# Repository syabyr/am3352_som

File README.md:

# am3352_som

#### 管脚定义

|管脚|定义|定义|管脚|
|----|---|----|---|
|1|GND|GND|2|
|3|LCD_DATA4|LCD_DATA8|4|
|5|GND|LCD_DATA5|6|
|7|LCD_DATA0|GND|8|
|9|LCD_DATA1|LCD_DATA2|10|
|11|GND|LCD_DATA6|12|
|13|LCD_PCLK|GND|14|
|15|LCD_VSYNC|LCD_DATA3|16|
|17|GND|LCD_DATA7|18|
|19|LCD_DATA14|GND|20|
|21|LCD_DATA11|LCD_HSYNC|22|
|23|GND|LCD_DATA15|24|
|25|LCD_DATA13|GND|26|
|27|LCD_DATA10|LCD_AC_BIAS_EN|28|
|29|GND|GPMC_AD8|30|
|31|LCD_DATA12|GND|32|
|33|LCD_DATA9|GPMC_AD9|34|
|35|GND|GPMC_AD10|36|
|37|GPMC_CLK|GND|38|
|39|GPMC_AD11|GPMC_13|40|
|41|GND|GPMC_12|42|
|43|GPMC_AD14|GND|44|
|45|GPMC_AD15|GPMC_A0|46|
|47|GND|GPMC_A4|48|
|49|GPMC_A2|GND|50|
|51|GPMC_A5|GPMC_A3|52|
|53|GND|GPMC_A1|54|
|55|GPMC_A6|GND|56|
|57|GPMC_A8|GPMC_A7|58|
|59|GND|GPMC_A10|60|
|61|GPMC_A9|GND|62|
|63|GPMC_A11|GPMC_BEn1|64|
|65|GND|USB1_VBUS|66|
|67|USB1_DP|GND|68|
|69|USB1_DM|USB0_VBUS|70|
|71|GND|USB0_ID|72|
||||
|73|USB1_ID|GND|74|
|75|USB1_CE|USB0_CE|76|
|77|GND|MDIO|78|
|79|USB0_DP|GND|80|
|81|USB0_DM|MDC|82|
|83|GND|MII1_RXD0|84|
|85|MII1_RXD3|GND|86|
|87|MII1_RX_CLK|MII1_RXD2|88|
|89|GND|MII1_RXD1|90|
|91|MII1_RX_DV|GND|92|
|93|MII1_TX_CLK|MII1_TXD2|94|
|95|GND|MII1_TXD0|96|
|97|MII1_TXD3|GND|98|
|99|MII1_TX_EN|MII1_TXD1|100|
|101|GND|MII1_RX_ER|102|
|103|RMII1_REF_CLK|GND|104|
|105|MMC0_CMD|MII1_COL|106|
|107|GND|MII1_CRS|108|
|109|MMC0_DAT2|GND|110|
|111|MMC0_DAT3|MMC0_DAT0|112|
|113|GND|MMC0_CLK|114|
|115|UART0_RTSn|GND|116|
|117|UART1_CSTn|MMC0_DAT1|118|
|119|GND|USB0_DRVVBUS|120|
|121|UART1_RTSn|GND|122|
|123|ECAP0_IN_PWM0_OUT|USB1_DRVVBUS|124|
|125|GND|UART0_TXD|126|
|127|I2C0_SDA|GND|128|
|129|EXTINTn|UART0_RXD|130|
|131|GND|UART1_RXD|132|
|133|SPI0_D0|GND|134|
|135|SPI0_SCLK|UART1_TXD|136|
|137|GND|I2C0_SCL|138|
|139|SPI0_D0|GND|140|
|141|SPI0_CS0|SPI0_CS1|142|
|143|GND|XDMA_EVENT_INTR1|144|
|145|EMU1|GND|146|
|147|MCASP0_AHCLKX|EMU0|148|
|149|GND|MCASP0_AXR1|150|
|151|MCASP0_FSX|GND|152|
|153|MCASP0_ACLKX|MCASP0_FSR|154|
|155|GND|MCASP0_AXR0|156|
|157|MCASP0_ACLKR|GND|158|
|159|TCK|MCASP0_AHCLKR|160|
|161|GND|TMS|162|
|163|TDI|GND|164|
|165|TDO|AIN7|166|
|167|GND|AIN4|168|
|169|TRSTn|GND|170|
|171|WARMRSTn|AIN5|172|
|173|GND|AIN6|174|
|175|PMIC_POWER_EN|GND|176|
|177|RTC_PWRONRSTn|AIN1|178|
|179|GND|AIN3|180|
|181|EXT_WAKEUP|GND|182|
|183|VDDS_RTC|AIN2|184|
|185|GND|AIN0|186|
|187||GND|188|
|189|VREFP|VCC|190|
|191|VCC|VCC|192|
|193|VCC|VCC|194|
|195|VCC|VCC|196|
|197|VCC|VCC|198|
|199|VCC|VCC|200|
|201|VCC|VCC|202|
|203|VCC|VCC|204|

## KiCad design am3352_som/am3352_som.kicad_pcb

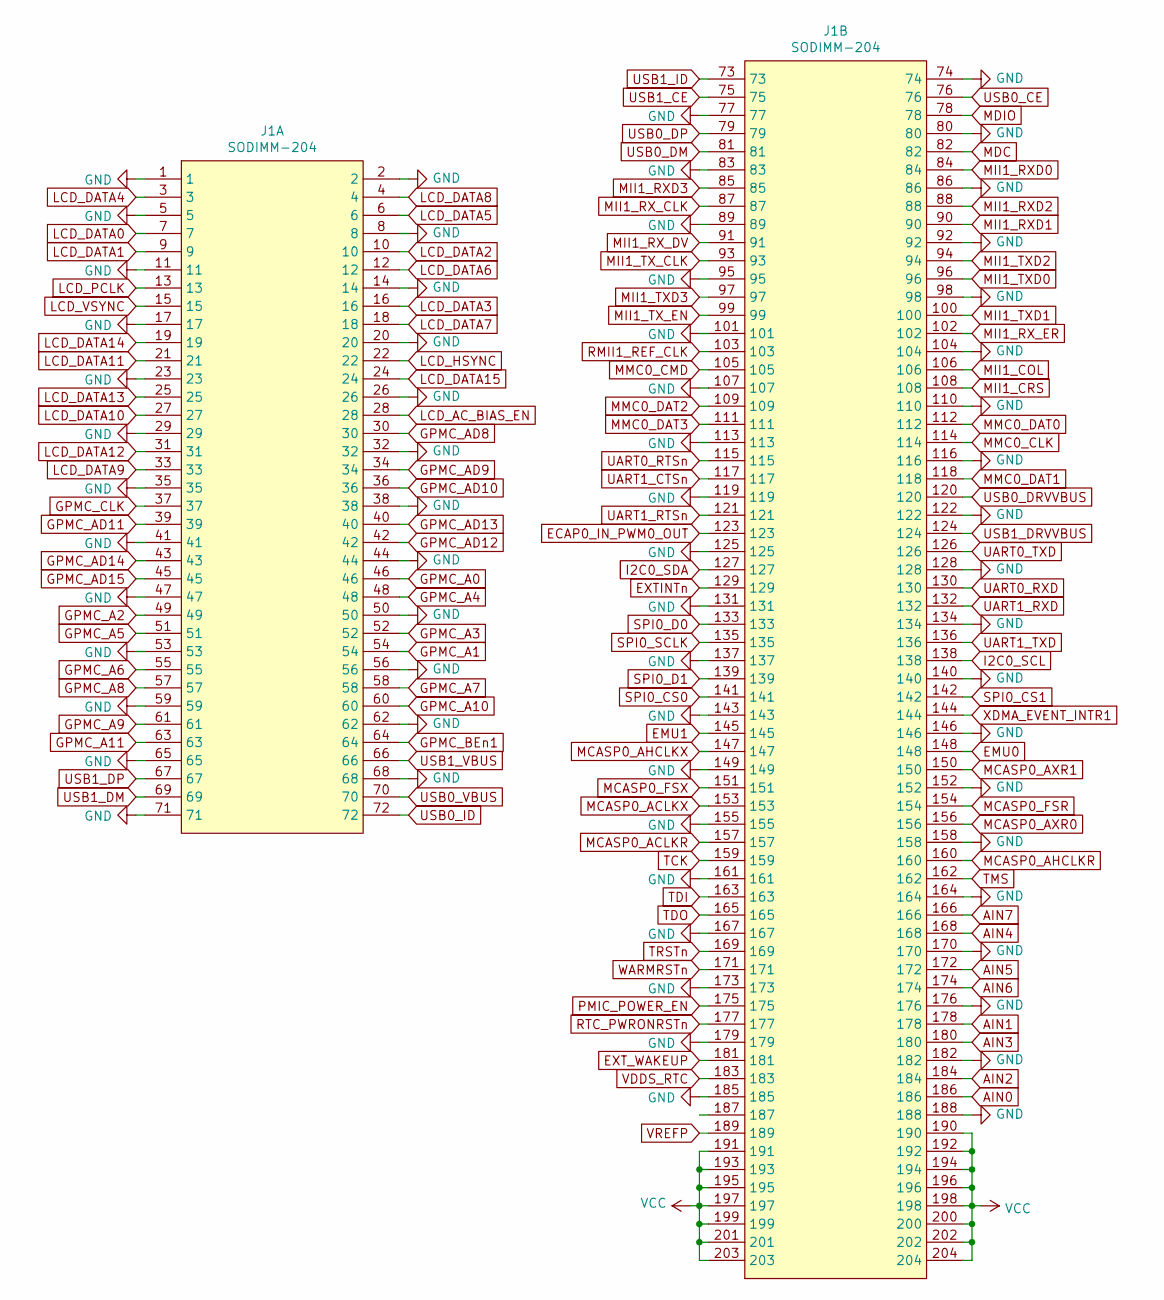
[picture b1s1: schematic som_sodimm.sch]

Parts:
J1: SODIMM-204; Socket_SODIMM_DDR3_TE_2013289_Debug

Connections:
AIN0: J1.186
AIN1: J1.178
AIN2: J1.184
AIN3: J1.180
AIN4: J1.168
AIN5: J1.172
AIN6: J1.174
AIN7: J1.166
ECAP0_IN_PWM0_OUT: J1.123
EMU0: J1.148
EMU1: J1.145
EXTINTn: J1.129
EXT_WAKEUP: J1.181
GND: J1.1, J1.2, J1.5, J1.8, J1.11, J1.14, J1.17, J1.20, J1.23, J1.26, J1.29, J1.32, J1.35, J1.38, J1.41, J1.44, J1.47, J1.50, J1.53, J1.56, J1.59, J1.62, J1.65, J1.68, J1.71, J1.74, J1.77, J1.80, J1.83, J1.86, J1.89, J1.92, J1.95, J1.98, J1.101, J1.104, J1.107, J1.110, J1.113, J1.116, J1.119, J1.122, J1.125, J1.128, J1.131, J1.134, J1.137, J1.140, J1.143, J1.146, J1.149, J1.152, J1.155, J1.158, J1.161, J1.164, J1.167, J1.170, J1.173, J1.176, J1.179, J1.182, J1.185, J1.188; also elsewhere on the board
GPMC_A0: J1.46
GPMC_A1: J1.54
GPMC_A2: J1.49
GPMC_A3: J1.52
GPMC_A4: J1.48
GPMC_A5: J1.51
GPMC_A6: J1.55
GPMC_A7: J1.58
GPMC_A8: J1.57
GPMC_A9: J1.61
GPMC_A10: J1.60
GPMC_A11: J1.63
GPMC_AD8: J1.30
GPMC_AD9: J1.34
GPMC_AD10: J1.36
GPMC_AD11: J1.39
GPMC_AD12: J1.42
GPMC_AD13: J1.40
GPMC_AD14: J1.43
GPMC_AD15: J1.45
GPMC_BEn1: J1.64
GPMC_CLK: J1.37
I2C0_SCL: J1.138
I2C0_SDA: J1.127
LCD_AC_BIAS_EN: J1.28
LCD_DATA0: J1.7
LCD_DATA1: J1.9
LCD_DATA2: J1.10
LCD_DATA3: J1.16
LCD_DATA4: J1.3
LCD_DATA5: J1.6
LCD_DATA6: J1.12
LCD_DATA7: J1.18
LCD_DATA8: J1.4
LCD_DATA9: J1.33
LCD_DATA10: J1.27
LCD_DATA11: J1.21
LCD_DATA12: J1.31
LCD_DATA13: J1.25
LCD_DATA14: J1.19
LCD_DATA15: J1.24
LCD_HSYNC: J1.22
LCD_PCLK: J1.13
LCD_VSYNC: J1.15
MCASP0_ACLKR: J1.157
MCASP0_ACLKX: J1.153
MCASP0_AHCLKR: J1.160
MCASP0_AHCLKX: J1.147
MCASP0_AXR0: J1.156
MCASP0_AXR1: J1.150
MCASP0_FSR: J1.154
MCASP0_FSX: J1.151
MDC: J1.82
MDIO: J1.78
MII1_COL: J1.106
MII1_CRS: J1.108
MII1_RXD0: J1.84; also elsewhere on the board
MII1_RXD1: J1.90; also elsewhere on the board
MII1_RXD2: J1.88; also elsewhere on the board
MII1_RXD3: J1.85; also elsewhere on the board
MII1_RX_CLK: J1.87
MII1_RX_DV: J1.91; also elsewhere on the board
MII1_RX_ER: J1.102
MII1_TXD0: J1.96; also elsewhere on the board
MII1_TXD1: J1.100; also elsewhere on the board
MII1_TXD2: J1.94; also elsewhere on the board
MII1_TXD3: J1.97; also elsewhere on the board
MII1_TX_CLK: J1.93; also elsewhere on the board
MII1_TX_EN: J1.99; also elsewhere on the board
MMC0_CLK: J1.114; also elsewhere on the board
MMC0_CMD: J1.105; also elsewhere on the board
MMC0_DAT0: J1.112; also elsewhere on the board
MMC0_DAT1: J1.118; also elsewhere on the board
MMC0_DAT2: J1.109; also elsewhere on the board
MMC0_DAT3: J1.111; also elsewhere on the board
PMIC_POWER_EN: J1.175
RMII1_REF_CLK: J1.103
RTC_PWRONRSTn: J1.177
SPI0_CS0: J1.141
SPI0_CS1: J1.142
SPI0_D0: J1.133
SPI0_D1: J1.139
SPI0_SCLK: J1.135
TCK: J1.159
TDI: J1.163
TDO: J1.165
TMS: J1.162
TRSTn: J1.169
UART0_RTSn: J1.115
UART0_RXD: J1.130
UART0_TXD: J1.126
UART1_CTSn: J1.117
UART1_RTSn: J1.121
UART1_RXD: J1.132
UART1_TXD: J1.136
USB0_CE: J1.76
USB0_DM: J1.81; also elsewhere on the board
USB0_DP: J1.79; also elsewhere on the board
USB0_DRVVBUS: J1.120
USB0_ID: J1.72; also elsewhere on the board
USB0_VBUS: J1.70
USB1_CE: J1.75
USB1_DM: J1.69; also elsewhere on the board
USB1_DP: J1.67; also elsewhere on the board
USB1_DRVVBUS: J1.124
USB1_ID: J1.73
USB1_VBUS: J1.66
VCC: J1.190, J1.191, J1.192, J1.193, J1.194, J1.195, J1.196, J1.197, J1.198, J1.199, J1.200, J1.201, J1.202, J1.203, J1.204
VDDS_RTC: J1.183
VREFP: J1.189
WARMRSTn: J1.171
XDMA_EVENT_INTR1: J1.144

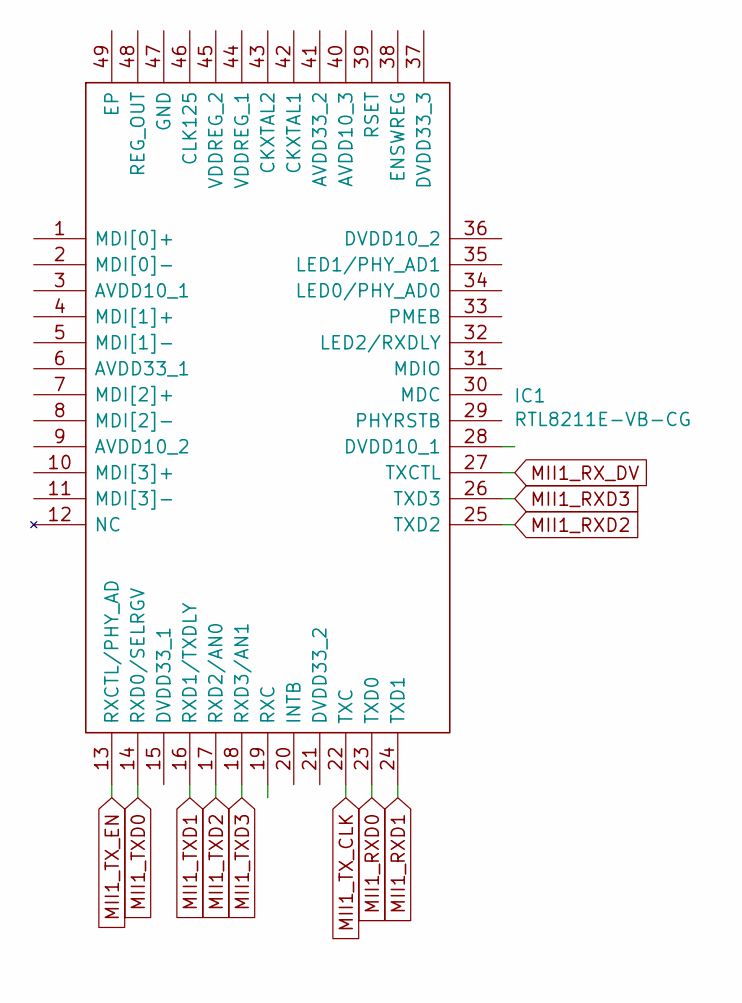
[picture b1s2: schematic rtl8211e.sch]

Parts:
IC1: RTL8211E-VB-CG; QFN40P600X600X100-49N; Manufacturer_Part_Number RTL8211E-VB-CG

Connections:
MII1_RXD0: IC1.23 (TXD0); also elsewhere on the board
MII1_RXD1: IC1.24 (TXD1); also elsewhere on the board
MII1_RXD2: IC1.25 (TXD2); also elsewhere on the board
MII1_RXD3: IC1.26 (TXD3); also elsewhere on the board
MII1_RX_DV: IC1.27 (TXCTL); also elsewhere on the board
MII1_TXD0: IC1.14 (RXD0/SELRGV); also elsewhere on the board
MII1_TXD1: IC1.16 (RXD1/TXDLY); also elsewhere on the board
MII1_TXD2: IC1.17 (RXD2/AN0); also elsewhere on the board
MII1_TXD3: IC1.18 (RXD3/AN1); also elsewhere on the board
MII1_TX_CLK: IC1.22 (TXC); also elsewhere on the board
MII1_TX_EN: IC1.13 (RXCTL/PHY_AD); also elsewhere on the board

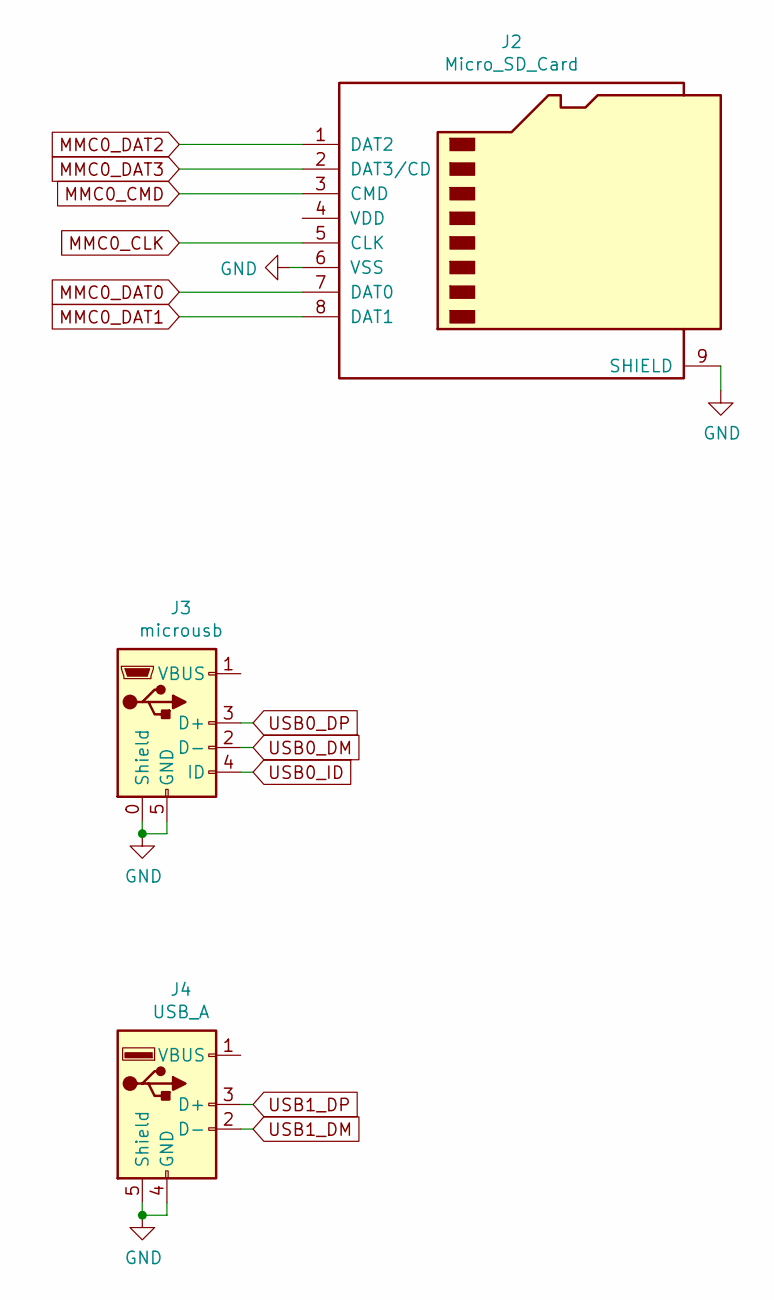
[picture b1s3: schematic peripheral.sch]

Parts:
J2: Micro_SD_Card; TFCARD
J3: microusb; MICRO-USB_MICRO-USB-17
J4: USB_A; USB_A_CONNFLY_DS1095-WNR0

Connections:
GND: J2.6 (VSS), J2.9 (SHIELD), J3.0 (Shield), J3.5 (GND), J4.4 (GND), J4.5 (Shield); also elsewhere on the board
MMC0_CLK: J2.5 (CLK); also elsewhere on the board
MMC0_CMD: J2.3 (CMD); also elsewhere on the board
MMC0_DAT0: J2.7 (DAT0); also elsewhere on the board
MMC0_DAT1: J2.8 (DAT1); also elsewhere on the board
MMC0_DAT2: J2.1 (DAT2); also elsewhere on the board
MMC0_DAT3: J2.2 (DAT3/CD); also elsewhere on the board
USB0_DM: J3.2 (D-); also elsewhere on the board
USB0_DP: J3.3 (D+); also elsewhere on the board
USB0_ID: J3.4 (ID); also elsewhere on the board
USB1_DM: J4.2 (D-); also elsewhere on the board
USB1_DP: J4.3 (D+); also elsewhere on the board

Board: 2 copper layers, 5 parts (0 on the bottom side), 24 nets, no tracks yet.

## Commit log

2021-05-24 datasheet
2021-05-26 pinout
2021-05-29 adjust
2021-06-18 som lcd
2021-06-18 refercence
